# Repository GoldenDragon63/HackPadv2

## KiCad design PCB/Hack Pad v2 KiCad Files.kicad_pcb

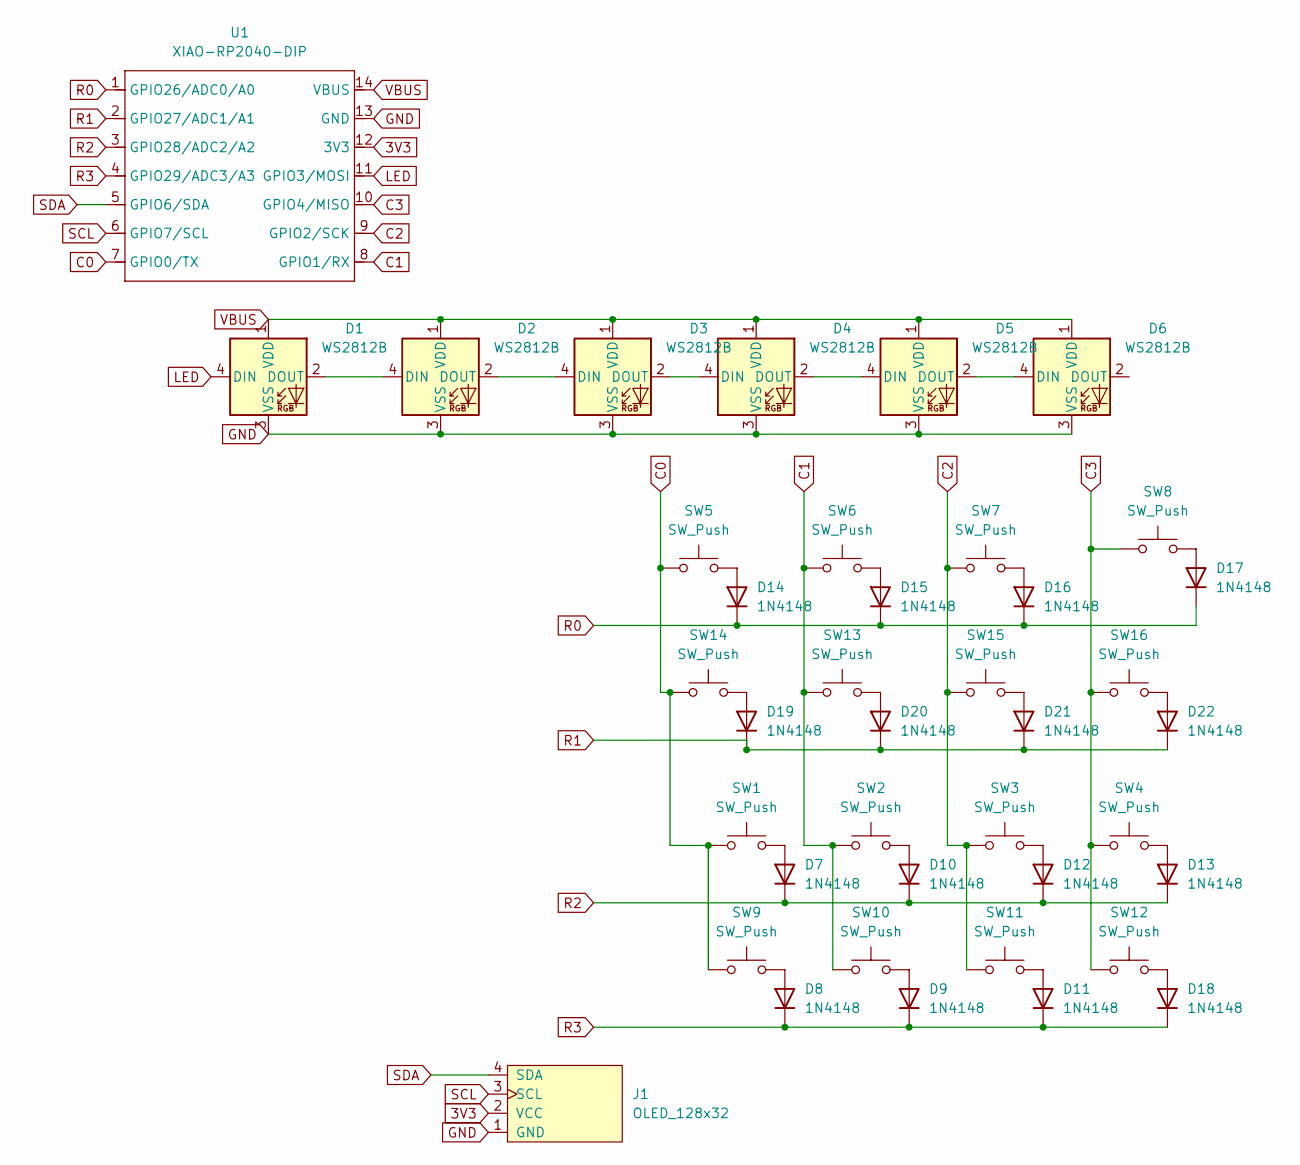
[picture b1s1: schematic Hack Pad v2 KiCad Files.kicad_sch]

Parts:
D1, D2, D3, D4, D5, D6: WS2812B; LED_WS2812B_PLCC4_5.0x5.0mm_P3.2mm
D7, D8, D9, D10, D11, D12, D13, D14, D15, D16, D17, D18, D19, D20, D21, D22: 1N4148; D_DO-35_SOD27_P7.62mm_Horizontal
J1: OLED_128x32
SW1, SW2, SW3, SW4, SW5, SW6, SW7, SW8, SW9, SW10, SW11, SW12, SW13, SW14, SW15, SW16: SW_Push; SW_Cherry_MX_1.00u_PCB
U1: XIAO-RP2040-DIP; XIAO-RP2040-SMD

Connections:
3V3: J1.2 (VCC), U1.12 (3V3)
C0: SW1.1, SW5.1, SW9.1, SW14.1, U1.7 (GPIO0/TX)
C1: SW2.1, SW6.1, SW10.1, SW13.1, U1.8 (GPIO1/RX)
C2: SW3.1, SW7.1, SW11.1, SW15.1, U1.9 (GPIO2/SCK)
C3: SW4.1, SW8.1, SW12.1, SW16.1, U1.10 (GPIO4/MISO)
GND: D1.3 (VSS), D2.3 (VSS), D3.3 (VSS), D4.3 (VSS), D5.3 (VSS), D6.3 (VSS), J1.1 (GND), U1.13 (GND)
LED: D1.4 (DIN), U1.11 (GPIO3/MOSI)
unnamed: D1.2 (DOUT), D2.4 (DIN)
unnamed: D2.2 (DOUT), D3.4 (DIN)
unnamed: D3.2 (DOUT), D4.4 (DIN)
unnamed: D4.2 (DOUT), D5.4 (DIN)
unnamed: D5.2 (DOUT), D6.4 (DIN)
unnamed: D7.2 (A), SW1.2
unnamed: D8.2 (A), SW9.2
unnamed: D9.2 (A), SW10.2
unnamed: D10.2 (A), SW2.2
unnamed: D11.2 (A), SW11.2
unnamed: D12.2 (A), SW3.2
unnamed: D13.2 (A), SW4.2
unnamed: D14.2 (A), SW5.2
unnamed: D15.2 (A), SW6.2
unnamed: D16.2 (A), SW7.2
unnamed: D17.2 (A), SW8.2
unnamed: D18.2 (A), SW12.2
unnamed: D19.2 (A), SW14.2
unnamed: D20.2 (A), SW13.2
unnamed: D21.2 (A), SW15.2
unnamed: D22.2 (A), SW16.2
R0: D14.1 (K), D15.1 (K), D16.1 (K), D17.1 (K), U1.1 (GPIO26/ADC0/A0)
R1: D19.1 (K), D20.1 (K), D21.1 (K), D22.1 (K), U1.2 (GPIO27/ADC1/A1)
R2: D7.1 (K), D10.1 (K), D12.1 (K), D13.1 (K), U1.3 (GPIO28/ADC2/A2)
R3: D8.1 (K), D9.1 (K), D11.1 (K), D18.1 (K), U1.4 (GPIO29/ADC3/A3)
SCL: J1.3 (SCL), U1.6 (GPIO7/SCL)
SDA: J1.4 (SDA), U1.5 (GPIO6/SDA)
VBUS: D1.1 (VDD), D2.1 (VDD), D3.1 (VDD), D4.1 (VDD), D5.1 (VDD), D6.1 (VDD), U1.14 (VBUS)

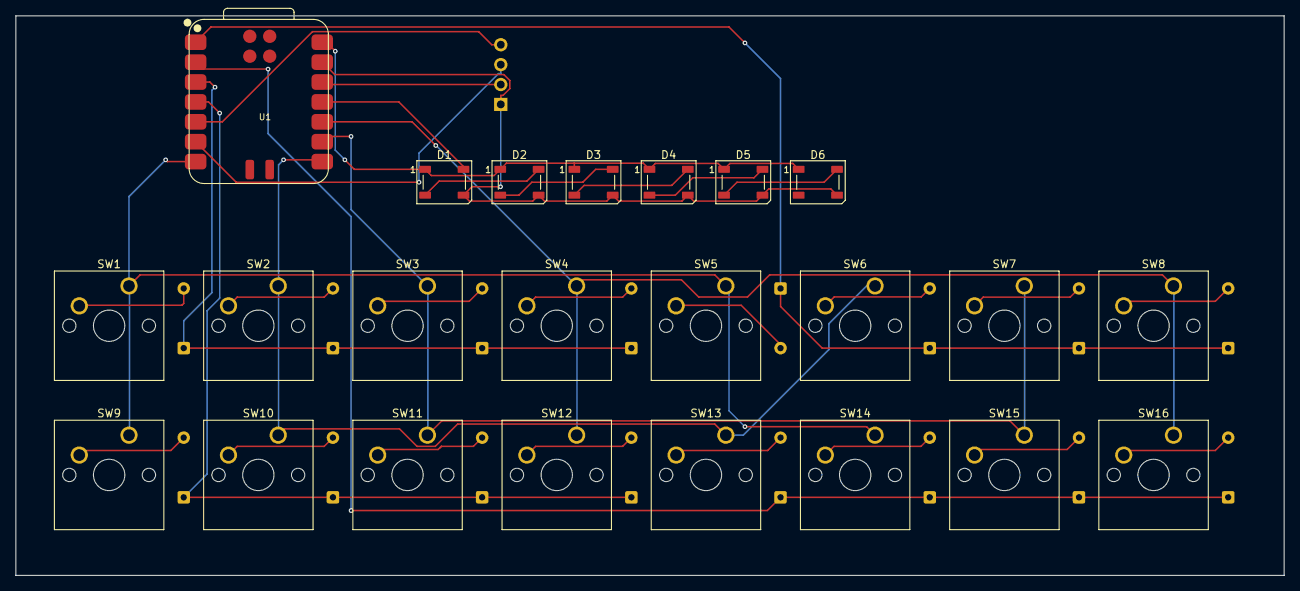
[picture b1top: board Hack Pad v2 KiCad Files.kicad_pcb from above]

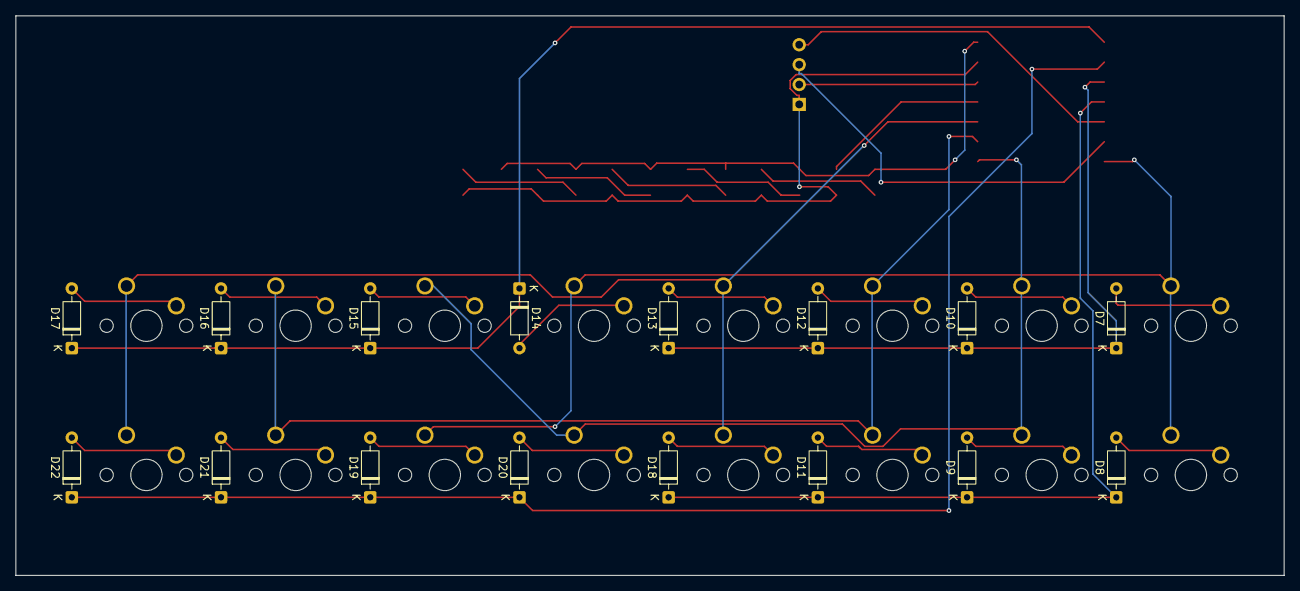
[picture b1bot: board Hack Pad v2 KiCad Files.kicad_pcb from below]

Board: 2 copper layers, 161.9 x 71.4 mm, 40 parts (16 on the bottom side), 35 nets.

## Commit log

2025-06-23 PCB Files
2025-06-23 Firmware
